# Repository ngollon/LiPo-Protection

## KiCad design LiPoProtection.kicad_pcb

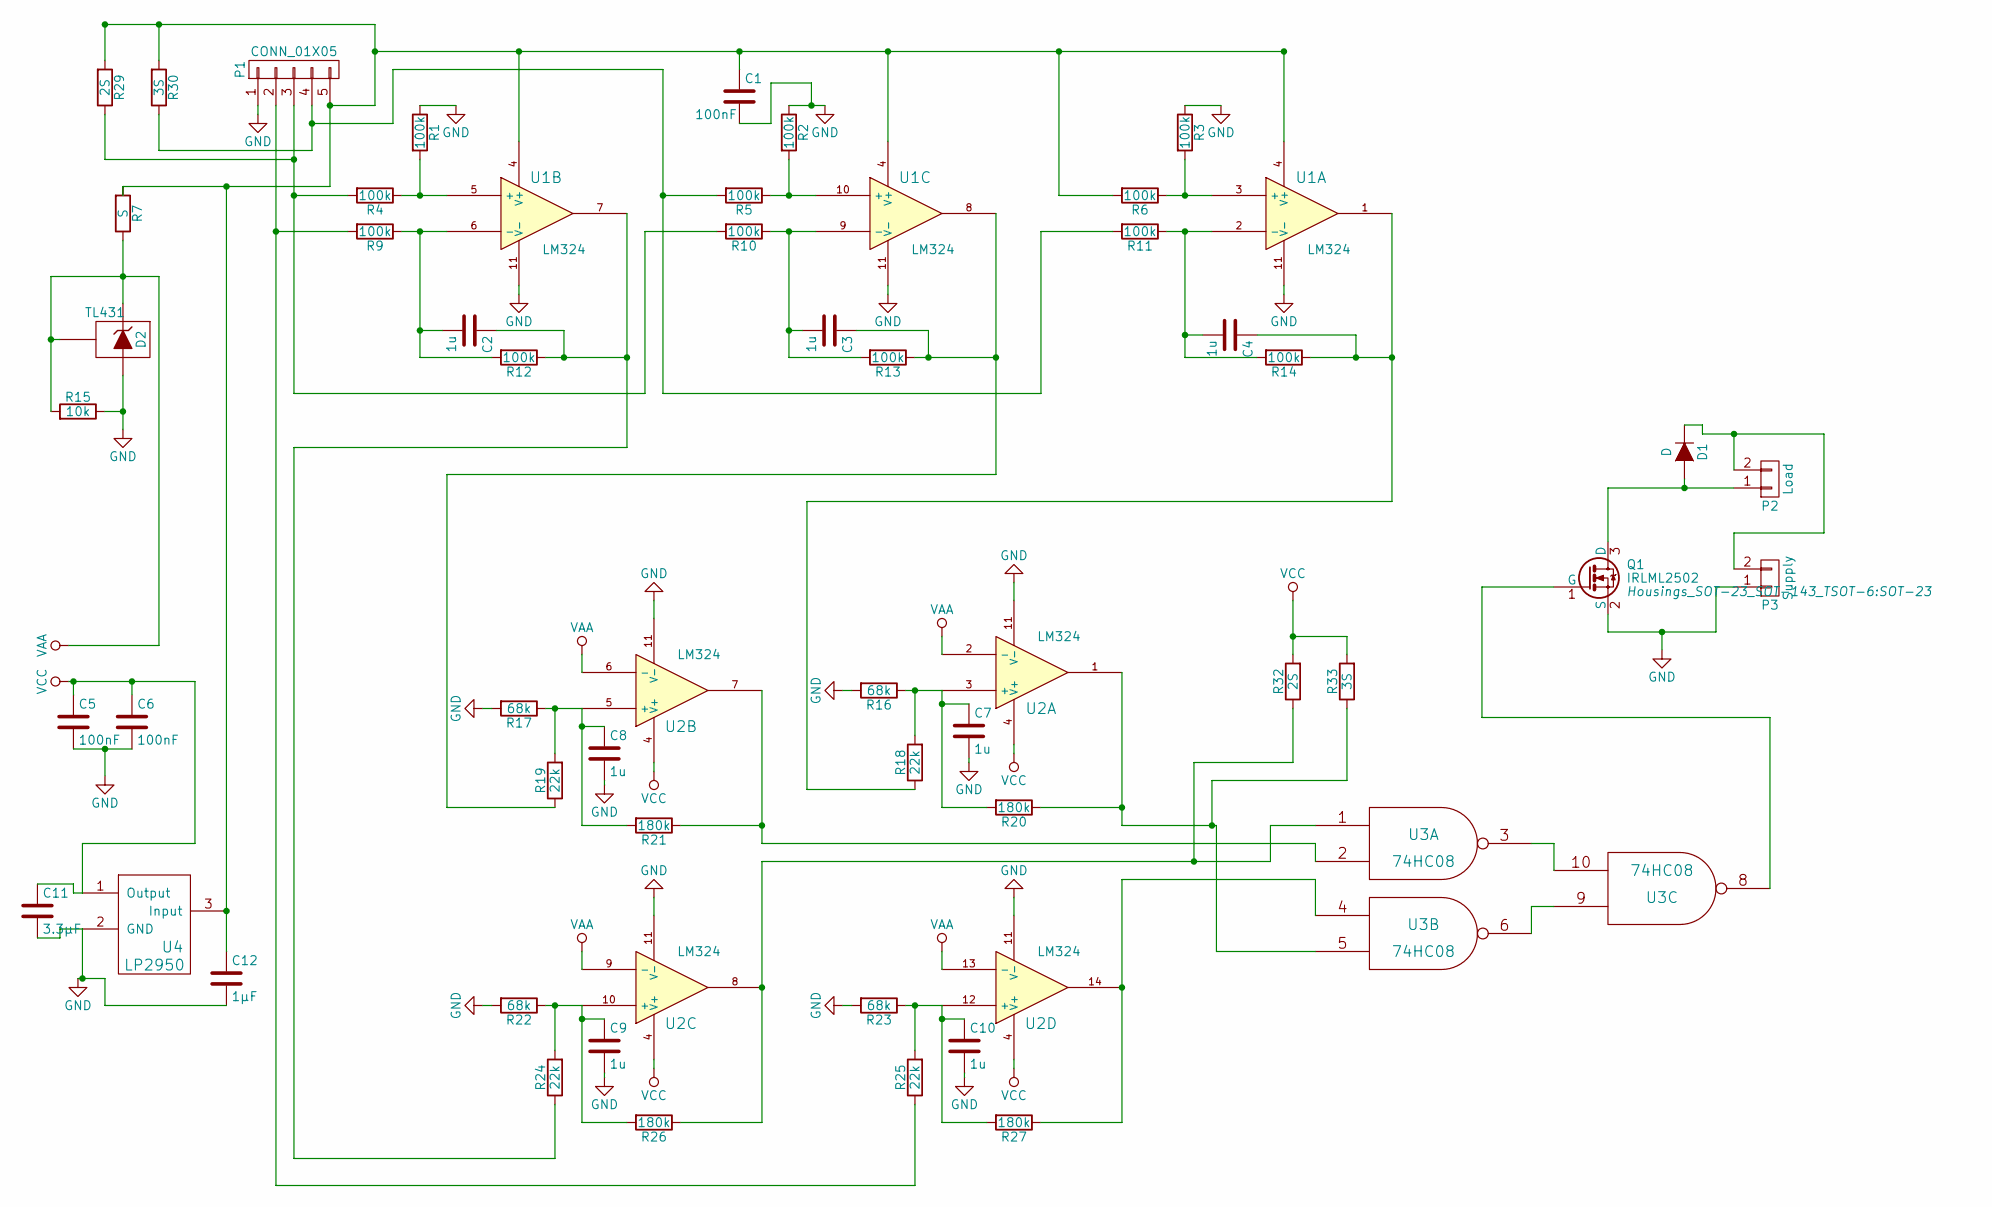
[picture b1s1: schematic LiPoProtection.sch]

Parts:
C1, C5, C6: 100nF; C_0805_HandSoldering
C2, C3, C4, C7, C8, C9, C10: 1u; C_0805_HandSoldering
C11: 3.3µF; C_0603_HandSoldering
C12: 1µF; C_0805_HandSoldering
D1: D; Diode_DO-41_SOD81_Horizontal_RM10
D2: TL431; SOT-23_Handsoldering
P1: CONN_01X05; Pin_Header_Straight_1x05
P2: Load; Pin_Header_Straight_1x02
P3: Supply; Pin_Header_Straight_1x02
Q1: IRLML2502; SOT-23
R1, R2, R3, R4, R5, R6, R9, R10, R11, R12, R13, R14: 100k; R_0805_HandSoldering
R7: S; R_0805_HandSoldering
R15: 10k; R_0805_HandSoldering
R16, R17, R22, R23: 68k; R_0805_HandSoldering
R18, R19, R24, R25: 22k; R_0805_HandSoldering
R20, R21, R26, R27: 180k; R_0805_HandSoldering
R29, R32: 2S; R_0805_HandSoldering
R30, R33: 3S; R_0805_HandSoldering
U1, U2: LM324; SOIC-14_N
U3: 74HC08; SOIC-14_N
U4: LP2950; TO-92_Inline_Narrow_Oval

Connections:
GND: C1.2, C5.2, C6.2, C7.2, C8.2, C9.2, C10.2, C11.2, C12.2, D2.3 (A), P1.1, P3.1, Q1.2 (S), R1.1, R2.1, R3.1, R15.1, R16.2, R17.2, R22.2, R23.2, U1.11 (V-), U2.11 (V-), U3.7 (GND), U4.2 (GND)
unnamed: C1.1, C12.1, P1.5, R6.2, R7.2, R29.2, R30.2, U1.4 (V+), U4.3 (Input)
unnamed: C2.1, R12.1, R24.1, U1.7
unnamed: C2.2, R9.1, R12.2, U1.6 (-)
unnamed: C3.1, R13.1, R19.1, U1.8
unnamed: C3.2, R10.1, R13.2, U1.9 (-)
unnamed: C4.1, R14.1, R18.1, U1.1
unnamed: C4.2, R11.1, R14.2, U1.2 (-)
unnamed: C7.1, R16.1, R18.2, R20.2, U2.3 (+)
unnamed: C8.1, R17.1, R19.2, R21.2, U2.5 (+)
unnamed: C9.1, R22.1, R24.2, R26.2, U2.10 (+)
unnamed: C10.1, R23.1, R25.2, R27.2, U2.12 (+)
unnamed: D1.1 (K), P2.2, P3.2
unnamed: D1.2 (A), P2.1, Q1.3 (D)
unnamed: P1.2, R9.2, R25.1
unnamed: P1.3, R4.2, R10.2, R29.1
unnamed: P1.4, R5.2, R11.2, R30.1
unnamed: Q1.1 (G), U3.8
unnamed: R1.2, R4.1, U1.5 (+)
unnamed: R2.2, R5.1, U1.10 (+)
unnamed: R3.2, R6.1, U1.3 (+)
unnamed: R20.1, R33.1, U2.1, U3.5
unnamed: R21.1, U2.7, U3.2
unnamed: R26.1, R32.1, U2.8, U3.1
unnamed: R27.1, U2.14, U3.4
unnamed: U3.6, U3.9
unnamed: U3.3, U3.10
VAA: D2.1 (K), D2.2 (REF), R7.1, R15.2, U2.2 (-), U2.6 (-), U2.9 (-), U2.13 (-)
VCC: C5.1, C6.1, C11.1, R32.2, R33.2, U2.4 (V+), U3.14 (VCC), U4.1 (Output)

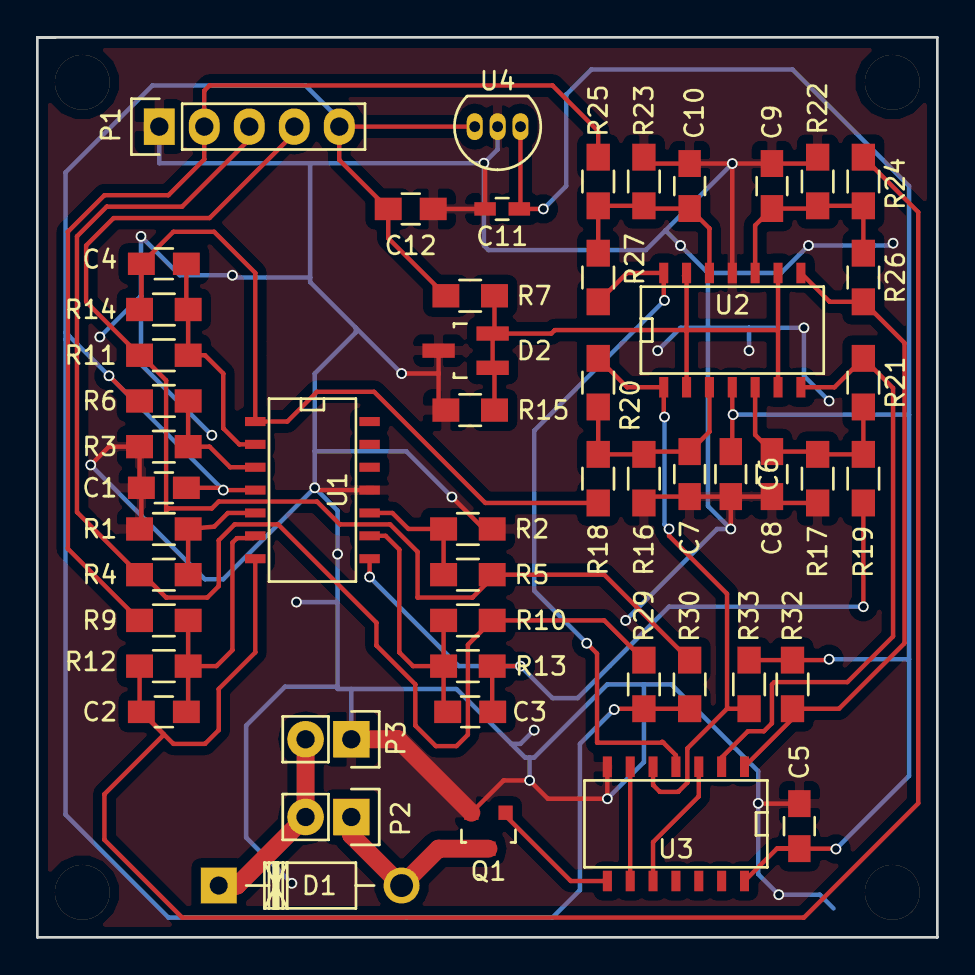
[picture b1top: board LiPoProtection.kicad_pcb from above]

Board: 2 copper layers, 50.0 x 50.0 mm, 52 parts (0 on the bottom side), 29 nets.

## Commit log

2015-09-14 :space_invader: Added .gitattributes & .gitignore files
2015-09-14 Added mass areas
2015-09-14 Moved supply and load pins
2015-09-15 Added libraries, added flyout diode
2015-09-15 Added a view vias
2015-09-16 Better trace placement
2015-09-16 Finishing touches, ordered.
